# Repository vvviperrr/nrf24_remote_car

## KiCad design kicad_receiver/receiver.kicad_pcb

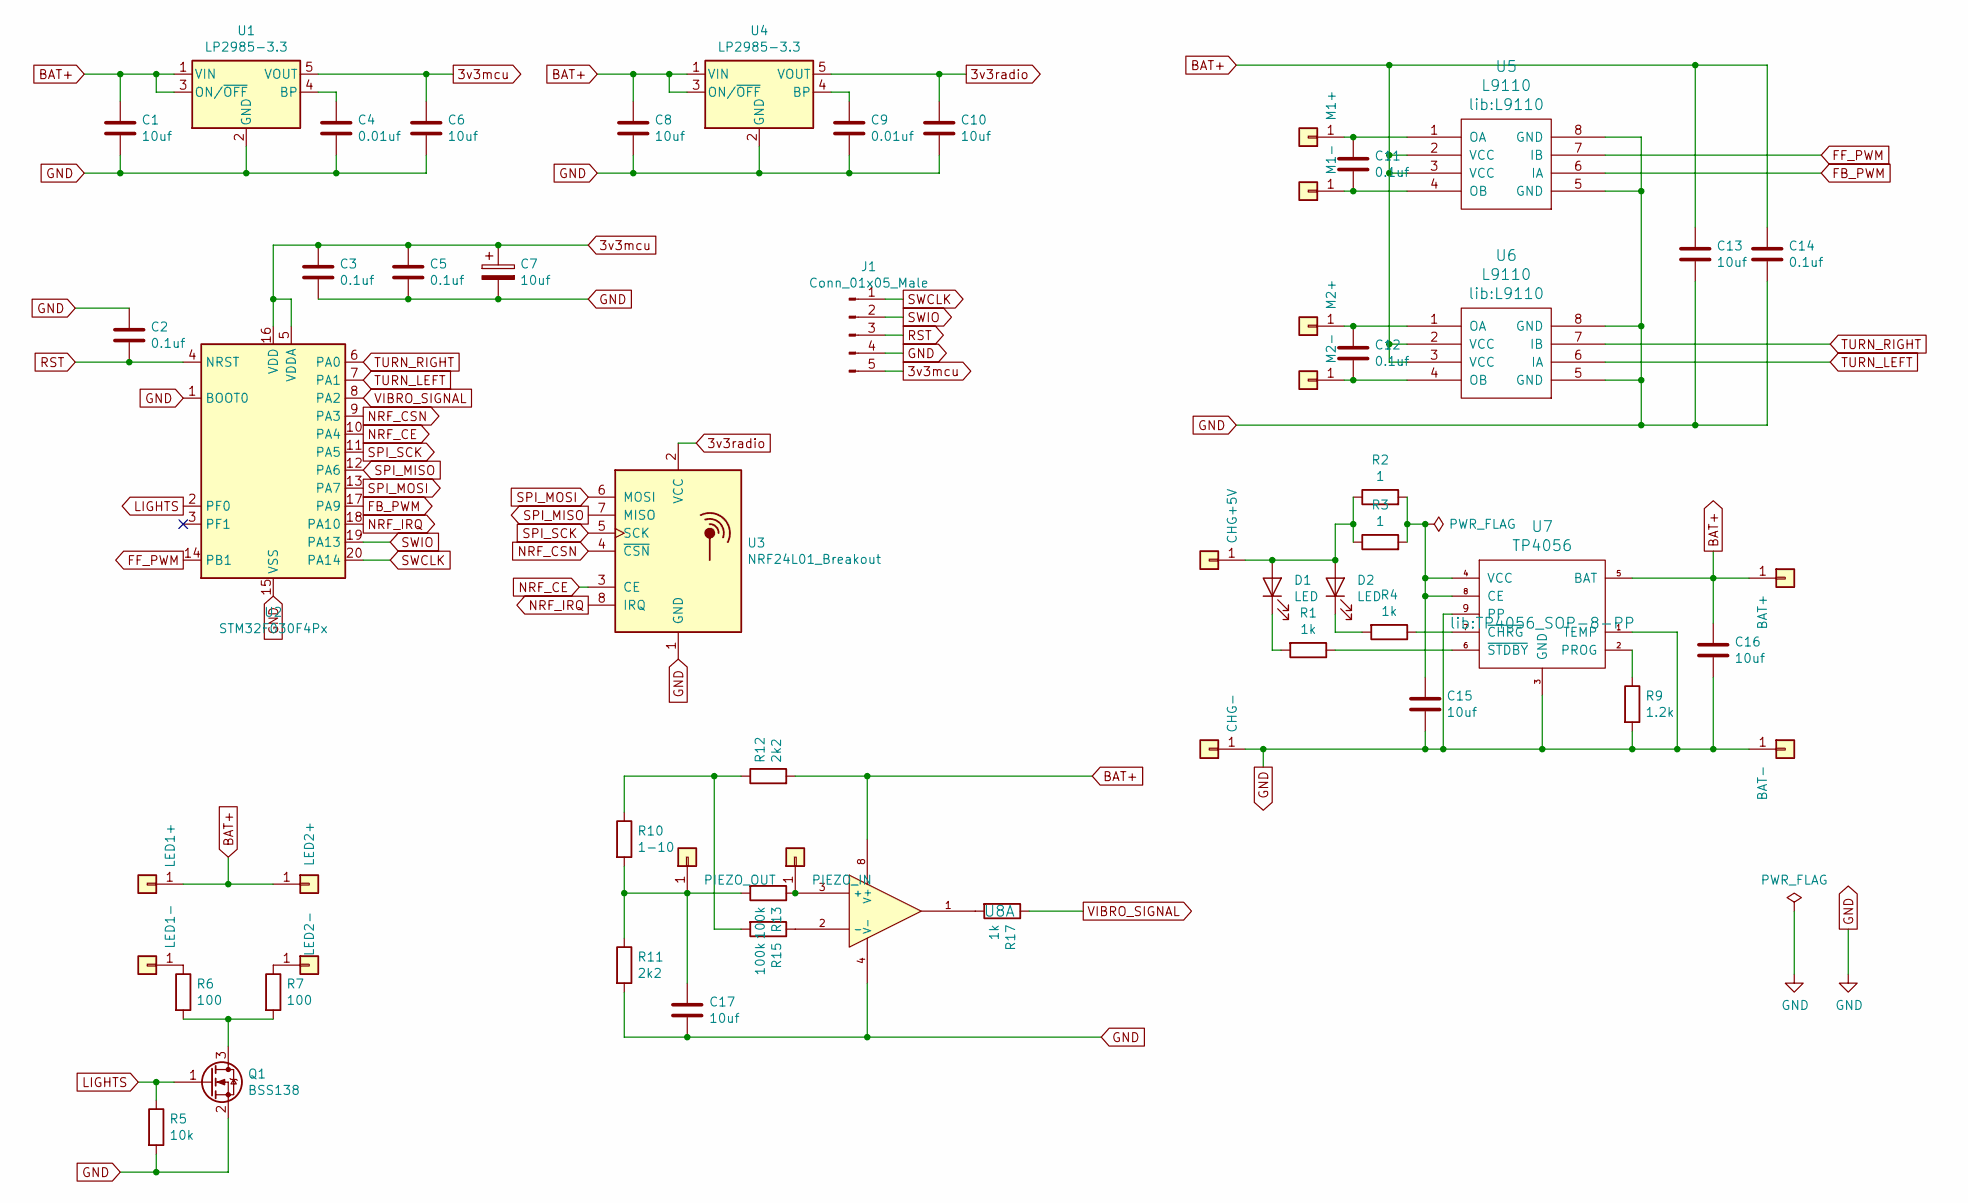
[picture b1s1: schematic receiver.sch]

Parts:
C1, C6, C8, C10, C13, C15, C16, C17: 10uf; C_0805_2012Metric_Pad1.15x1.40mm_HandSolder
C2: 0.1uf; C_0603_1608Metric_Pad1.05x0.95mm_HandSolder
C3, C5, C11, C12, C14: 0.1uf; C_0805_2012Metric_Pad1.15x1.40mm_HandSolder
C4, C9: 0.01uf; C_0805_2012Metric_Pad1.15x1.40mm_HandSolder
C7: 10uf; CP_EIA-3216-18_Kemet-A_Pad1.58x1.35mm_HandSolder
D1, D2: LED; LED_0603_1608Metric_Pad1.05x0.95mm_HandSolder
J1: Conn_01x05_Male; PinHeader_1x05_P2.54mm_Vertical
J2: M1+; TestPoint_THTPad_4.0x4.0mm_Drill2.0mm
J3: M1-; TestPoint_THTPad_4.0x4.0mm_Drill2.0mm
J4: M2+; TestPoint_THTPad_4.0x4.0mm_Drill2.0mm
J5: M2-; TestPoint_THTPad_4.0x4.0mm_Drill2.0mm
J6: CHG+5V; TestPoint_THTPad_4.0x4.0mm_Drill2.0mm
J7: CHG-; TestPoint_THTPad_4.0x4.0mm_Drill2.0mm
J8: BAT+; TestPoint_THTPad_4.0x4.0mm_Drill2.0mm
J9: BAT-; TestPoint_THTPad_4.0x4.0mm_Drill2.0mm
J10: PIEZO_OUT; TestPoint_THTPad_4.0x4.0mm_Drill2.0mm
J11: PIEZO_IN; TestPoint_THTPad_4.0x4.0mm_Drill2.0mm
J12: LED1+; TestPoint_THTPad_4.0x4.0mm_Drill2.0mm
J13: LED1-; TestPoint_THTPad_4.0x4.0mm_Drill2.0mm
J14: LED2+; TestPoint_THTPad_4.0x4.0mm_Drill2.0mm
J15: LED2-; TestPoint_THTPad_4.0x4.0mm_Drill2.0mm
Q1: BSS138; SOT-23
R1, R4, R17: 1k; R_0603_1608Metric_Pad1.05x0.95mm_HandSolder
R2, R3: 1; R_0805_2012Metric_Pad1.15x1.40mm_HandSolder
R5: 10k; R_0603_1608Metric_Pad1.05x0.95mm_HandSolder
R6, R7: 100; R_0603_1608Metric_Pad1.05x0.95mm_HandSolder
R9: 1.2k; R_0603_1608Metric_Pad1.05x0.95mm_HandSolder
R10: 1-10; R_0603_1608Metric_Pad1.05x0.95mm_HandSolder
R11, R12: 2k2; R_0603_1608Metric_Pad1.05x0.95mm_HandSolder
R13, R15: 100k; R_0603_1608Metric_Pad1.05x0.95mm_HandSolder
U1, U4: LP2985-3.3; SOT-23-5_HandSoldering
U2: STM32F030F4Px; TSSOP-20_4.4x6.5mm_P0.65mm
U3: NRF24L01_Breakout; NRF24L01-SMD
U5, U6: L9110
U7: TP4056; TP4056_SOP-8-PP
U8: LM358; SOIC-8_3.9x4.9mm_P1.27mm

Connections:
3v3mcu: C3.1, C5.1, C6.1, C7.1, J1.5, U1.5 (VOUT), U2.5 (VDDA), U2.16 (VDD)
3v3radio: C10.1, U3.2 (VCC), U4.5 (VOUT)
BAT+: C1.1, C8.1, C13.1, C14.1, C16.1, J8.1, J12.1, J14.1, R12.2, U1.1 (VIN), U1.3 (ON/~OFF~), U4.1 (VIN), U4.3 (ON/~OFF~), U5.2 (VCC), U5.3 (VCC), U6.2 (VCC), U6.3 (VCC), U7.5 (BAT), U8.8 (V+)
FB_PWM: U2.17 (PA9), U5.6 (IA)
FF_PWM: U2.14 (PB1), U5.7 (IB)
GND: C1.2, C2.1, C3.2, C4.2, C5.2, C6.2, C7.2, C8.2, C9.2, C10.2, C13.2, C14.2, C15.2, C16.2, C17.2, J1.4, J7.1, J9.1, Q1.2 (S), R5.2, R9.2, R11.2, U1.2 (GND), U2.1 (BOOT0), U2.15 (VSS), U3.1 (GND), U4.2 (GND), U5.5 (GND), U5.8 (GND), U6.5 (GND), U6.8 (GND), U7.1 (TEMP), U7.3 (GND), U7.9 (PP), U8.4 (V-)
LIGHTS: Q1.1 (G), R5.1, U2.2 (PF0)
NRF_CE: U2.10 (PA4), U3.3 (CE)
NRF_CSN: U2.9 (PA3), U3.4 (~CSN)
NRF_IRQ: U2.18 (PA10), U3.8 (IRQ)
unnamed: C4.1, U1.4 (BP)
unnamed: C9.1, U4.4 (BP)
unnamed: C11.1, J2.1, U5.1 (OA)
unnamed: C11.2, J3.1, U5.4 (OB)
unnamed: C12.1, J4.1, U6.1 (OA)
unnamed: C12.2, J5.1, U6.4 (OB)
unnamed: C15.1, R2.2, R3.2, U7.4 (VCC), U7.8 (CE)
unnamed: C17.1, J10.1, R10.2, R11.1, R13.2
unnamed: D1.1 (K), R1.2
unnamed: D1.2 (A), D2.2 (A), J6.1, R2.1, R3.1
unnamed: D2.1 (K), R4.2
unnamed: J11.1, R13.1, U8.3 (+)
unnamed: J13.1, R6.1
unnamed: J15.1, R7.1
unnamed: Q1.3 (D), R6.2, R7.2
unnamed: R1.1, U7.6 (~STDBY)
unnamed: R4.1, U7.7 (~CHRG)
unnamed: R9.1, U7.2 (PROG)
unnamed: R10.1, R12.1, R15.2
unnamed: R15.1, U8.2 (-)
unnamed: R17.2, U8.1
RST: C2.2, J1.3, U2.4 (NRST)
SPI_MISO: U2.12 (PA6), U3.7 (MISO)
SPI_MOSI: U2.13 (PA7), U3.6 (MOSI)
SPI_SCK: U2.11 (PA5), U3.5 (SCK)
SWCLK: J1.1, U2.20 (PA14)
SWIO: J1.2, U2.19 (PA13)
TURN_LEFT: U2.7 (PA1), U6.6 (IA)
TURN_RIGHT: U2.6 (PA0), U6.7 (IB)
VIBRO_SIGNAL: R17.1, U2.8 (PA2)

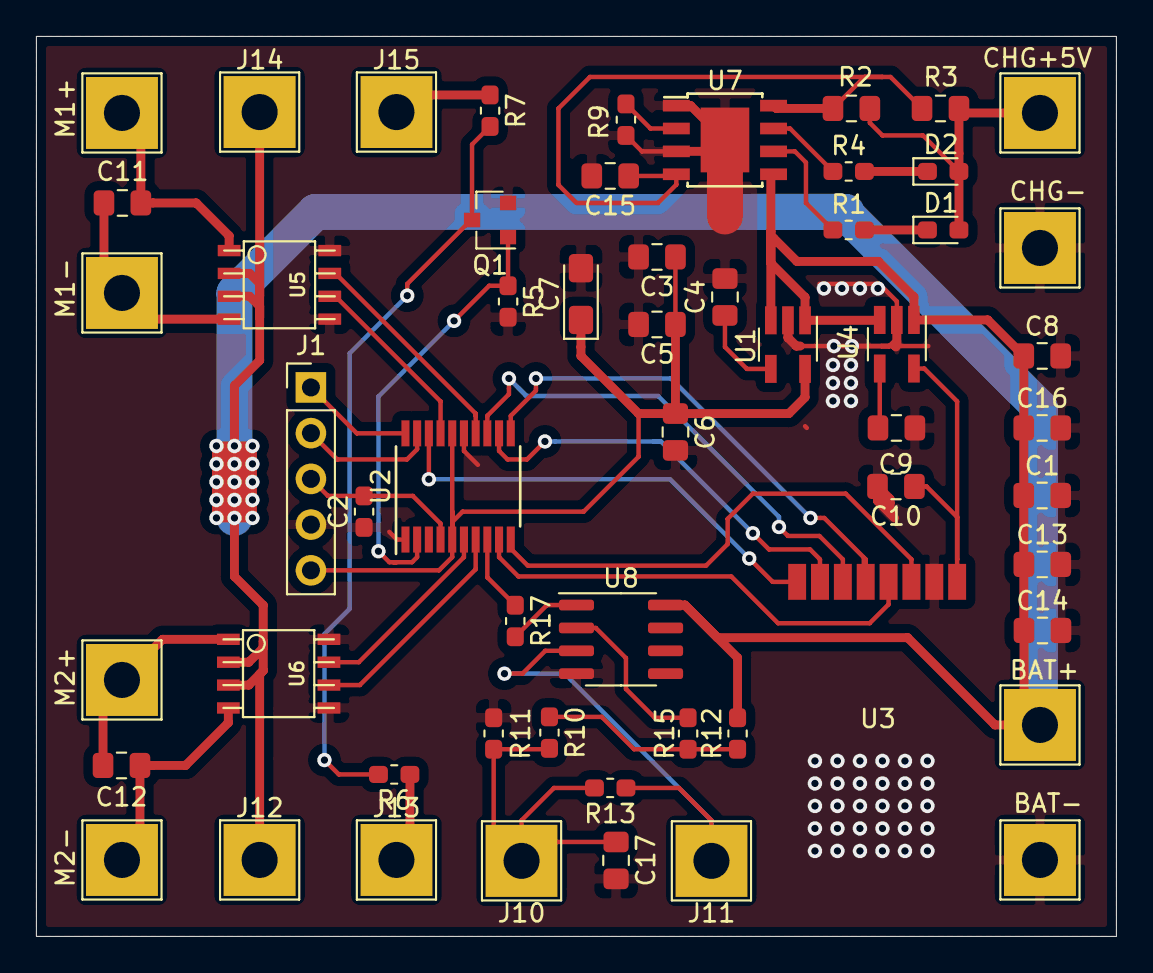
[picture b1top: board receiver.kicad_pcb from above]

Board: 2 copper layers, 60.0 x 50.0 mm, 57 parts (0 on the bottom side), 40 nets.

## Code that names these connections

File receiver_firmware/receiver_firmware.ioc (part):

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Mcu.Name=STM32F030F4Px
Mcu.Package=TSSOP20
Mcu.UserName=STM32F030F4Px
PA0.Signal=GPIO_Output
PA1.Signal=GPIO_Output
PA10.Signal=GPIO_Input
PA13.Mode=Serial_Wire
PA13.Signal=SYS_SWDIO
PA14.Mode=Serial_Wire
PA14.Signal=SYS_SWCLK
PA2.Mode=IN2
PA2.Signal=ADC_IN2
PA3.Signal=GPIO_Output
PA4.Signal=GPIO_Output
PA5.Mode=Full_Duplex_Master
PA5.Signal=SPI1_SCK
PA6.Mode=Full_Duplex_Master
PA6.Signal=SPI1_MISO
PA7.Mode=Full_Duplex_Master
PA7.Signal=SPI1_MOSI
PA9.Signal=S_TIM1_CH2
PB1.Signal=S_TIM3_CH4
PF0-OSC_IN.Signal=GPIO_Output
board=custom

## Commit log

2019-10-11 receiver initial commit
2019-10-11 more stuff added
2019-10-11 refactored
2019-10-12 place done
2019-10-13 fixed
2019-10-13 almost routed
2019-10-14 done!
2019-10-14 optocouples removed
2019-10-15 new route done
2019-10-15 mosfets added, piezo scheme added
2019-10-16 piezo route done
2019-10-16 mosfets removed, now use pure pwm signals
2019-10-18 lights added, new route complete
2019-10-18 layout refactored, logos added
2019-10-18 project renamed
2019-10-18 receiver firmware + cubex project added
2019-10-20 lib issue fixed
